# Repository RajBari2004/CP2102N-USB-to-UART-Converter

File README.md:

# CP2102N USB-to-UART Converter

<p align="center">
  <b>USB Type-C to UART Interface | CP2102N | Custom PCB | KiCad 9.0</b>
</p>

## 📌 Project Overview

This project is a **custom USB-to-UART converter PCB** designed around the **Silicon Labs CP2102N USB-to-UART bridge controller**.

The board provides a reliable interface between a **USB Type-C host** and external UART-based embedded systems. It is intended for applications such as **microcontroller programming, firmware development, serial debugging, hardware testing, and embedded-system communication**.

The complete hardware design, including the schematic and PCB layout, was developed using **KiCad 9.0**.

---

## ✨ Key Features

* 🔌 USB Type-C input interface
* 🔄 CP2102N USB-to-UART bridge
* 🛡️ USB D+/D− ESD protection
* ⚡ USB-C CC configuration resistors
* 💡 TX/RX activity indication LEDs
* 🔄 Hardware reset interface
* 🔋 Local power-supply decoupling
* 📡 External UART interface header
* 🧩 Compact custom PCB layout
* 🛠️ KiCad 9.0 schematic and PCB design
* 📦 Manufacturing-ready design workflow

---

## 🏗️ System Architecture

```text
                USB TYPE-C
                    │
             ┌──────┴──────┐
             │ USB D+ / D− │
             │ ESD Protect │
             └──────┬──────┘
                    │
                    ▼
              ┌───────────┐
              │  CP2102N  │
              │ USB → UART│
              └─────┬─────┘
                    │
              ┌─────┴─────┐
              │           │
             TX/RX       RST
              │           │
              ▼           ▼
        ┌────────────────────┐
        │   External UART    │
        │       Header       │
        └────────────────────┘
```

---

## 🔌 USB Type-C Interface

The USB interface is implemented using a **USB Type-C receptacle**.

The design includes:

* USB VBUS
* USB D+
* USB D−
* GND
* CC1 / CC2 configuration resistors
* USB ESD protection

The CC pins use **5.1 kΩ pull-down resistors** to configure the board as a USB sink/device.

The USB data lines are protected against electrostatic discharge before reaching the USB-to-UART controller.

---

## 🔄 CP2102N USB-to-UART Bridge

The core of the design is the **CP2102N USB-to-UART bridge controller**.

It performs the conversion between:

```text
USB
 │
 ▼
CP2102N
 │
 ▼
UART
```

This allows a computer to communicate with an external microcontroller or UART-based embedded system through a standard USB connection.

### UART Signals

| Signal | Function       |
| ------ | -------------- |
| TX     | UART Transmit  |
| RX     | UART Receive   |
| RST    | Hardware Reset |
| VBUS   | Supply         |
| GND    | Ground         |

---

## 💡 TX/RX Activity Indicators

Dedicated LEDs are included to provide visual indication of UART communication activity.

```text
CP2102N TX ──► TX LED
CP2102N RX ──► RX LED
```

This makes debugging and serial communication monitoring easier during hardware development.

---

## 🔋 Power & Decoupling

The design includes local bypass/decoupling capacitors around the CP2102N and USB supply.

The decoupling network helps reduce supply noise and provides transient current locally to the IC.

The design includes multiple **100 nF ceramic capacitors** for high-frequency supply decoupling.

---

## 🛡️ USB ESD Protection

ESD protection is implemented on the USB data interface to improve robustness against electrostatic discharge entering through the USB connector.

```text
USB-C
  │
  ├── D+ ──► ESD Protection ──► CP2102N
  │
  └── D− ──► ESD Protection ──► CP2102N
```

This provides an additional protection layer between the external USB connector and the USB interface circuitry.

---

## 📐 PCB Design

The PCB was designed using **KiCad 9.0 PCB Editor**.

The layout focuses on:

* Compact component placement
* Short USB data connections
* Practical routing
* Power decoupling
* Clear connector placement
* Accessible UART header
* Manufacturing-oriented PCB layout

### PCB Layout

### 3D Front View

### 3D Back View

---

## 📋 External UART Header

The board provides a dedicated **5-pin external interface**.

| Pin | Signal | Description   |
| --: | ------ | ------------- |
|   1 | GND    | Ground        |
|   2 | VBUS   | USB supply    |
|   3 | RX     | UART Receive  |
|   4 | TX     | UART Transmit |
|   5 | RST    | Reset         |

This header can be connected to external embedded platforms for development and debugging.

---

## 🧩 Hardware Components

| Component             | Function                  |
| --------------------- | ------------------------- |
| CP2102N               | USB-to-UART conversion    |
| USB Type-C Receptacle | USB connectivity          |
| ESD Protection        | USB data-line protection  |
| 5.1 kΩ Resistors      | USB-C CC configuration    |
| LEDs                  | TX/RX activity indication |
| Capacitors            | Supply decoupling         |
| UART Header           | External serial interface |

---

## 🛠️ Design Tools

| Tool                       | Purpose                |
| -------------------------- | ---------------------- |
| **KiCad 9.0**              | Schematic & PCB design |
| **KiCad Schematic Editor** | Circuit design         |
| **KiCad PCB Editor**       | PCB layout             |
| **KiCad 3D Viewer**        | PCB visualization      |

---

## 📁 Repository Structure

```text
CP2102N-USB-to-UART-Converter/
│
├── KiCad/
│   ├── USB To UART.kicad_pro
│   ├── USB To UART.kicad_sch
│   └── USB To UART.kicad_pcb
│
├── Images/
│   ├── schematic.png
│   ├── pcb_layout.png
│   ├── pcb_3d_front.png
│   └── pcb_3d_back.png
│
├── Gerber/
│   └── Manufacturing files
│
└── README.md
```

---

## 📷 Schematic

---

## 🎯 Applications

This converter can be used for:

* Microcontroller programming
* UART debugging
* Embedded firmware development
* Serial communication
* ESP8266 / ESP32 development
* Arduino development
* Bootloader interfaces
* Hardware testing
* Development-board debugging
* General USB-to-UART communication

---

## 🧠 Engineering Concepts Demonstrated

This project demonstrates practical experience with:

* USB Type-C interface design
* USB 2.0 D+/D− routing
* USB ESD protection
* USB-C CC configuration
* USB-to-UART conversion
* UART interface design
* Power-supply decoupling
* Indicator LED circuits
* Connector interfacing
* Schematic capture
* PCB component placement
* PCB routing
* Footprint selection
* PCB design verification
* KiCad 9.0 workflow

---

## 🚀 Future Improvements

Possible future revisions could include:

* USB-C overvoltage/overcurrent protection
* Improved ESD protection
* Configurable UART voltage levels
* Additional UART control signals
* Test points for critical signals
* Mounting holes
* Status/power indicator
* Improved high-speed USB layout optimization
* Production-oriented DFM review

---

## 📌 Project Status

**Status:** Hardware Design Completed

**Design Stage:** Schematic + PCB Layout

**EDA Tool:** KiCad 9.0

**Interface:** USB Type-C → UART

**USB-to-UART IC:** CP2102N

---

## 👨‍💻 Author

**Raj.B**

B.Tech — Electronics & Telecommunication Engineering

Interested in **Embedded Systems, PCB Design, Hardware Development, IoT, and Power Electronics**.

---

## 📄 License

This project is provided for educational, development, and portfolio purposes.

If you use or modify this design, please provide appropriate attribution to the original project.

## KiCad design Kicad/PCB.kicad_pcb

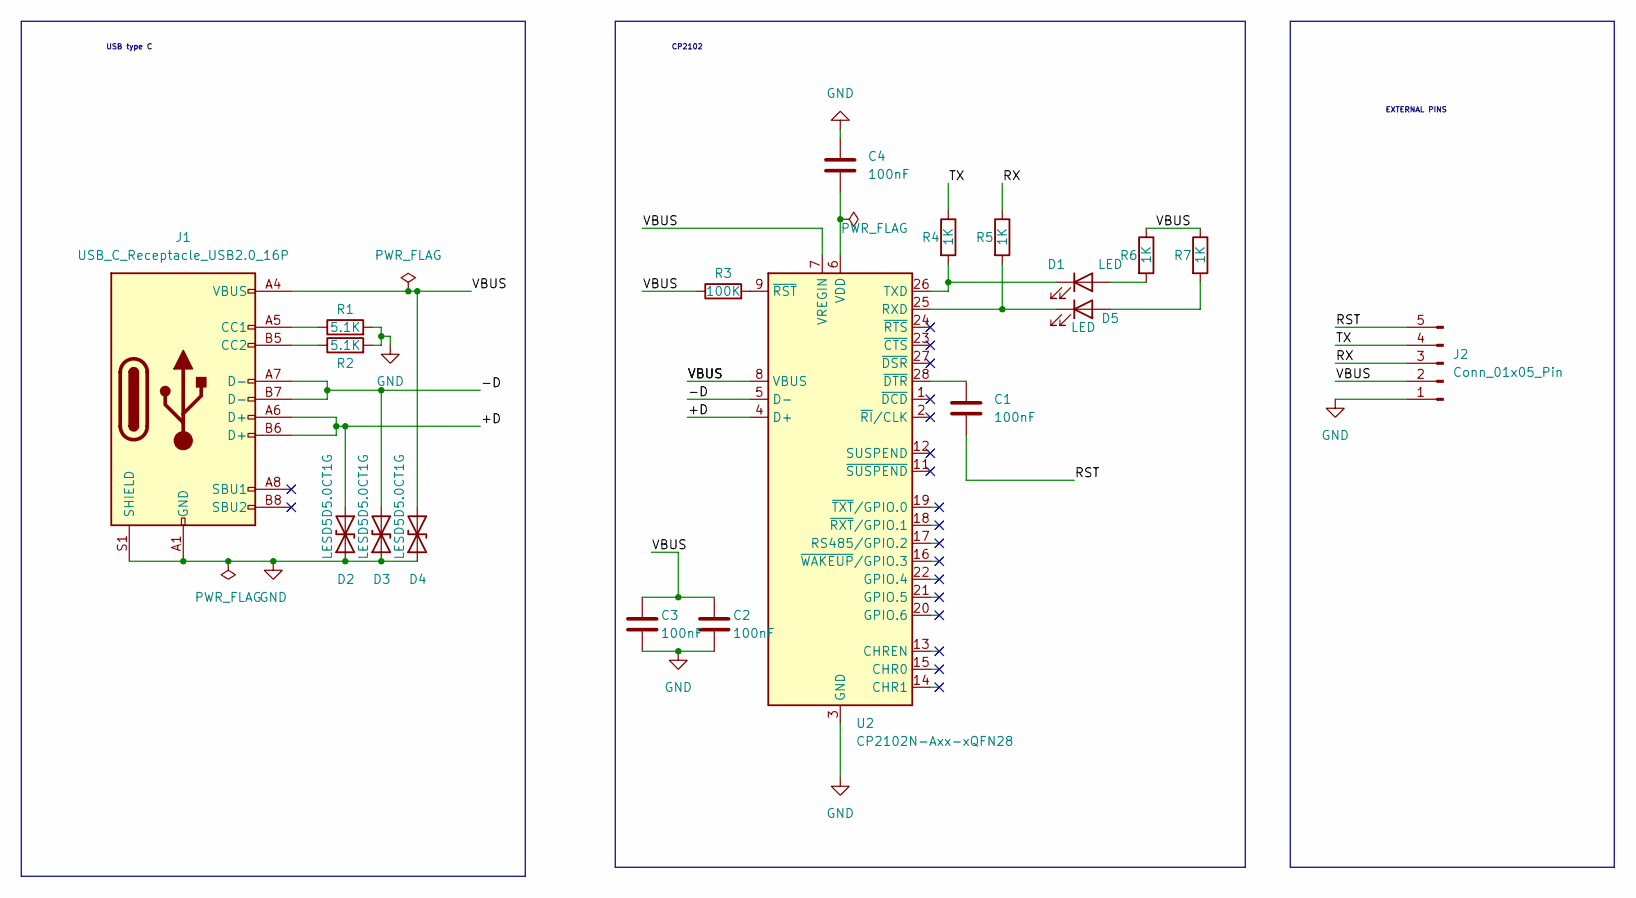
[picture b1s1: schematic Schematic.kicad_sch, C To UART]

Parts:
C1, C2, C3, C4: 100nF; C_0201_0603Metric
D1, D5: LED; LED_0201_0603Metric
D2, D3, D4: LESD5D5.0CT1G; D_SOD-523
J1: USB_C_Receptacle_USB2.0_16P; USB_C_Receptacle_GCT_USB4105-xx-A_16P_TopMnt_Horizontal
J2: Conn_01x05_Pin; PinHeader_1x05_P2.54mm_Horizontal
R1, R2: 5.1K; R_0201_0603Metric
R3: 100K; R_0201_0603Metric
R4, R5, R6, R7: 1K; R_0201_0603Metric
U2: CP2102N-Axx-xQFN28; QFN-28-1EP_5x5mm_P0.5mm_EP3.35x3.35mm

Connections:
/+D: D2.2 (A2), J1.A6 (D+), J1.B6 (D+), U2.4 (D+)
/-D: D3.2 (A2), J1.A7 (D-), J1.B7 (D-), U2.5 (D-)
/RST: C1.2, J2.5
/RX: J2.3, R5.1
/TX: J2.4, R4.1
/VBUS: C2.1, C3.1, D4.2 (A2), J1.A4 (VBUS), J1.A9 (VBUS), J1.B4 (VBUS), J1.B9 (VBUS), J2.2, R3.1, R6.1, R7.1, U2.7 (VREGIN), U2.8 (VBUS)
GND: C2.2, C3.2, C4.1, D2.1 (A1), D3.1 (A1), D4.1 (A1), J1.A1 (GND), J1.A12 (GND), J1.B1 (GND), J1.B12 (GND), J1.S1 (SHIELD), J2.1, R1.2, R2.2, U2.3 (GND), U2.29 (GND)
unnamed: D1.2 (A), R6.2
unnamed: D1.1 (K), R4.2, U2.26 (TXD)
unnamed: D5.2 (A), R7.2
unnamed: D5.1 (K), R5.2, U2.25 (RXD)
unnamed: J1.A5 (CC1), R1.1
unnamed: J1.B5 (CC2), R2.1
unnamed: C4.2, U2.6 (VDD)
unnamed: C1.1, U2.28 (~DTR)
unnamed: R3.2, U2.9 (~RST)

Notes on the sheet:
USB type C
EXTERNAL PINS
CP2102

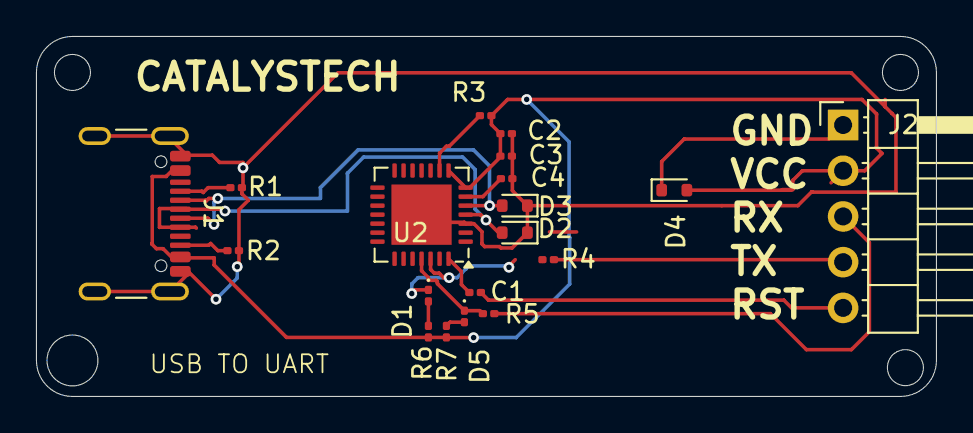
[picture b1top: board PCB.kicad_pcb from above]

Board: 2 copper layers, 50.0 x 20.0 mm, 19 parts (0 on the bottom side), 16 nets.
